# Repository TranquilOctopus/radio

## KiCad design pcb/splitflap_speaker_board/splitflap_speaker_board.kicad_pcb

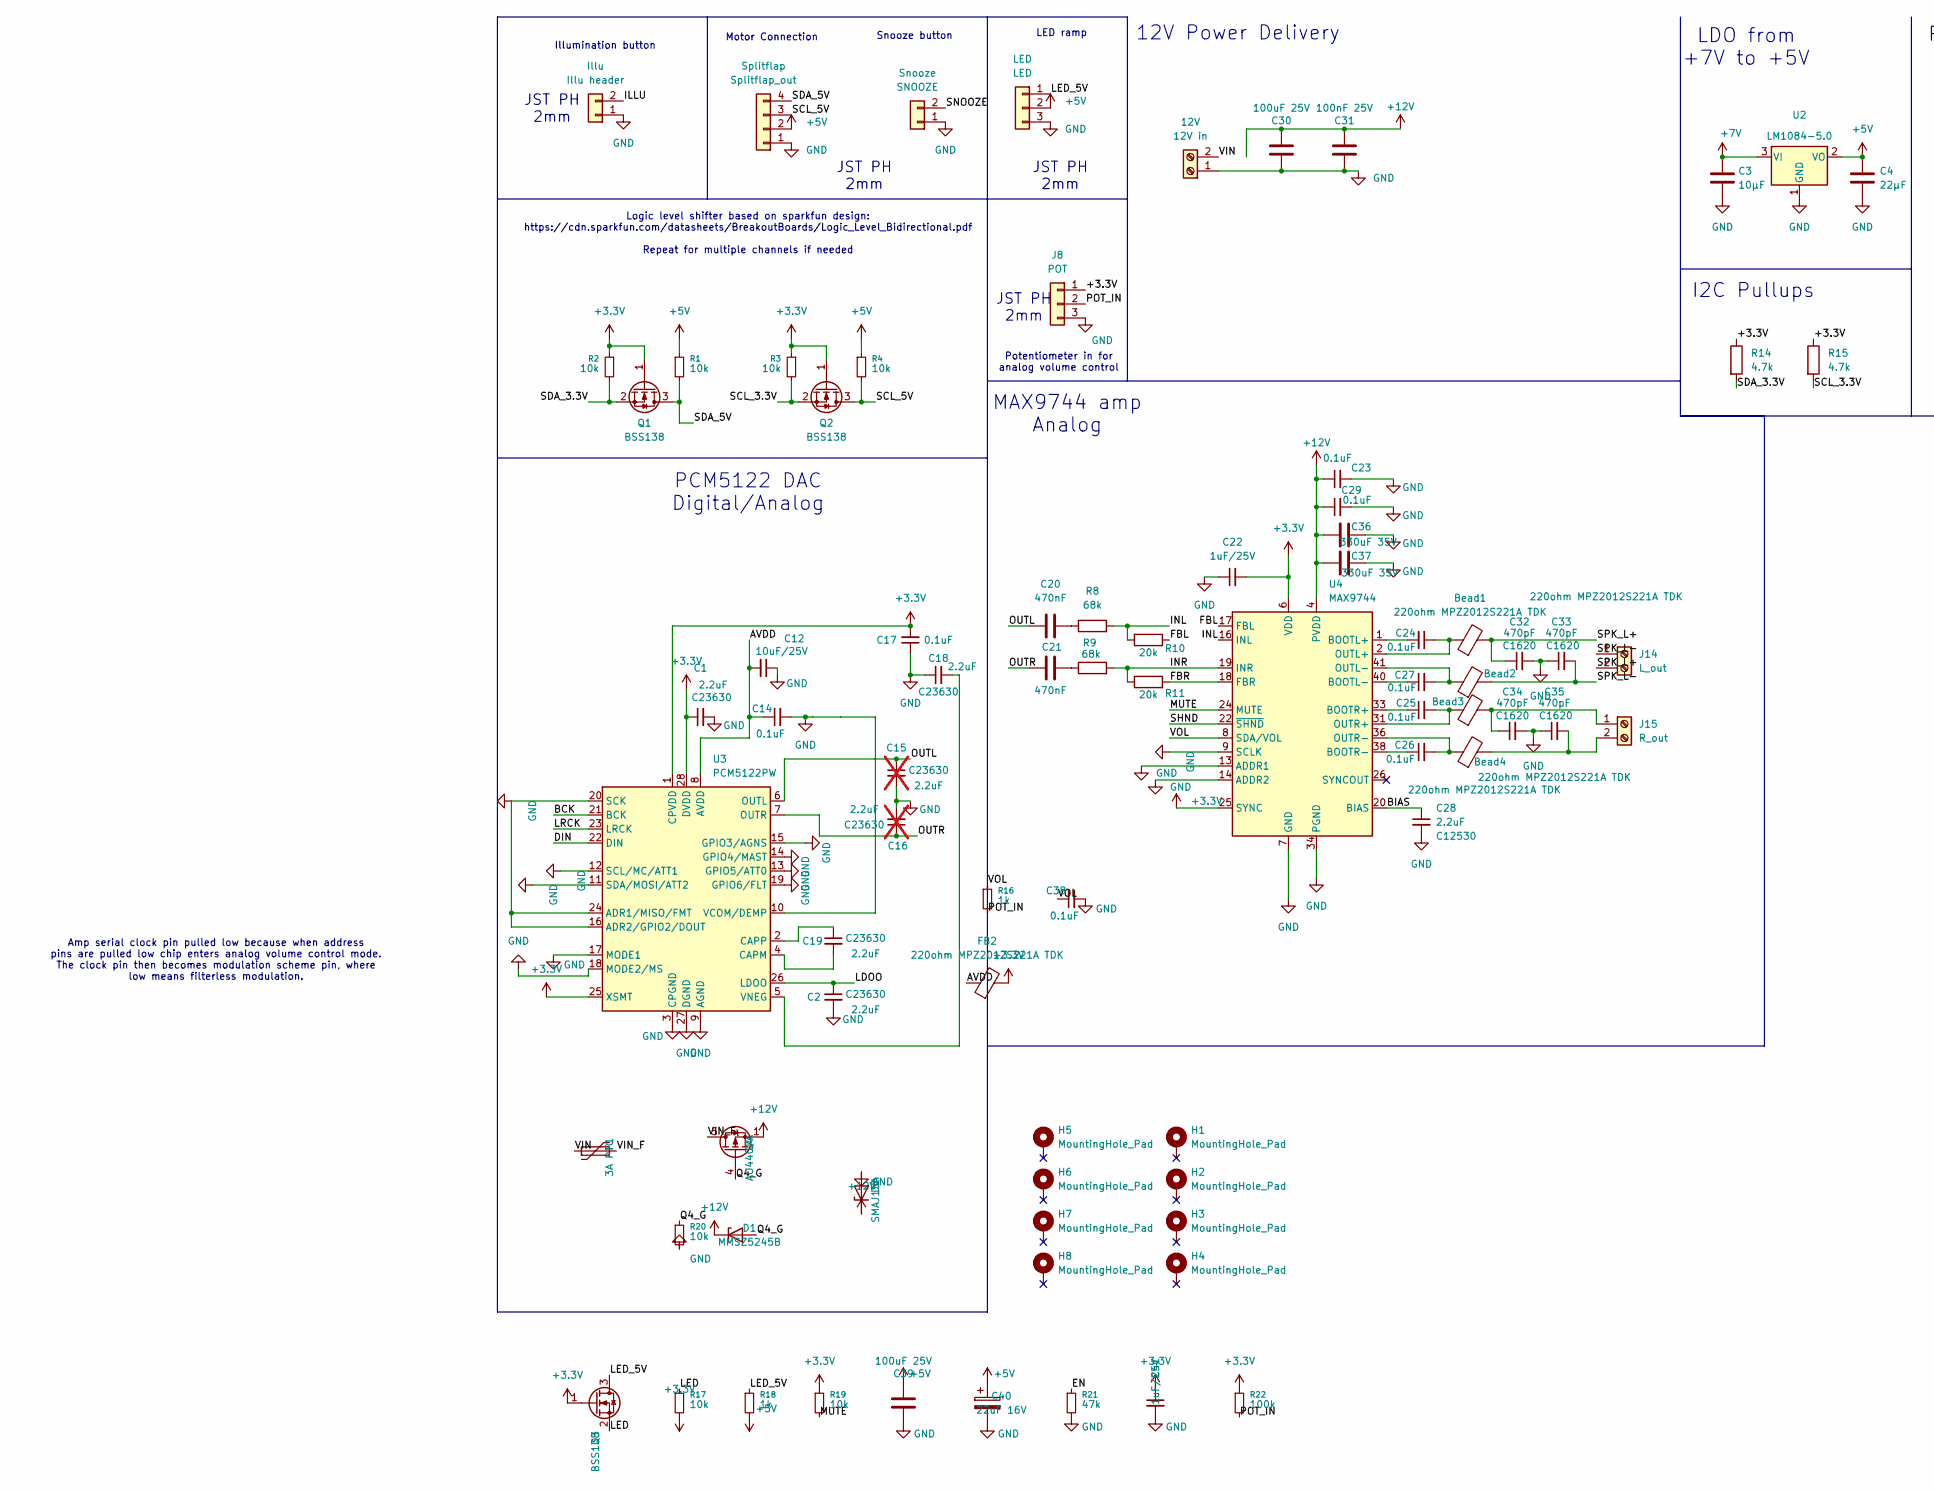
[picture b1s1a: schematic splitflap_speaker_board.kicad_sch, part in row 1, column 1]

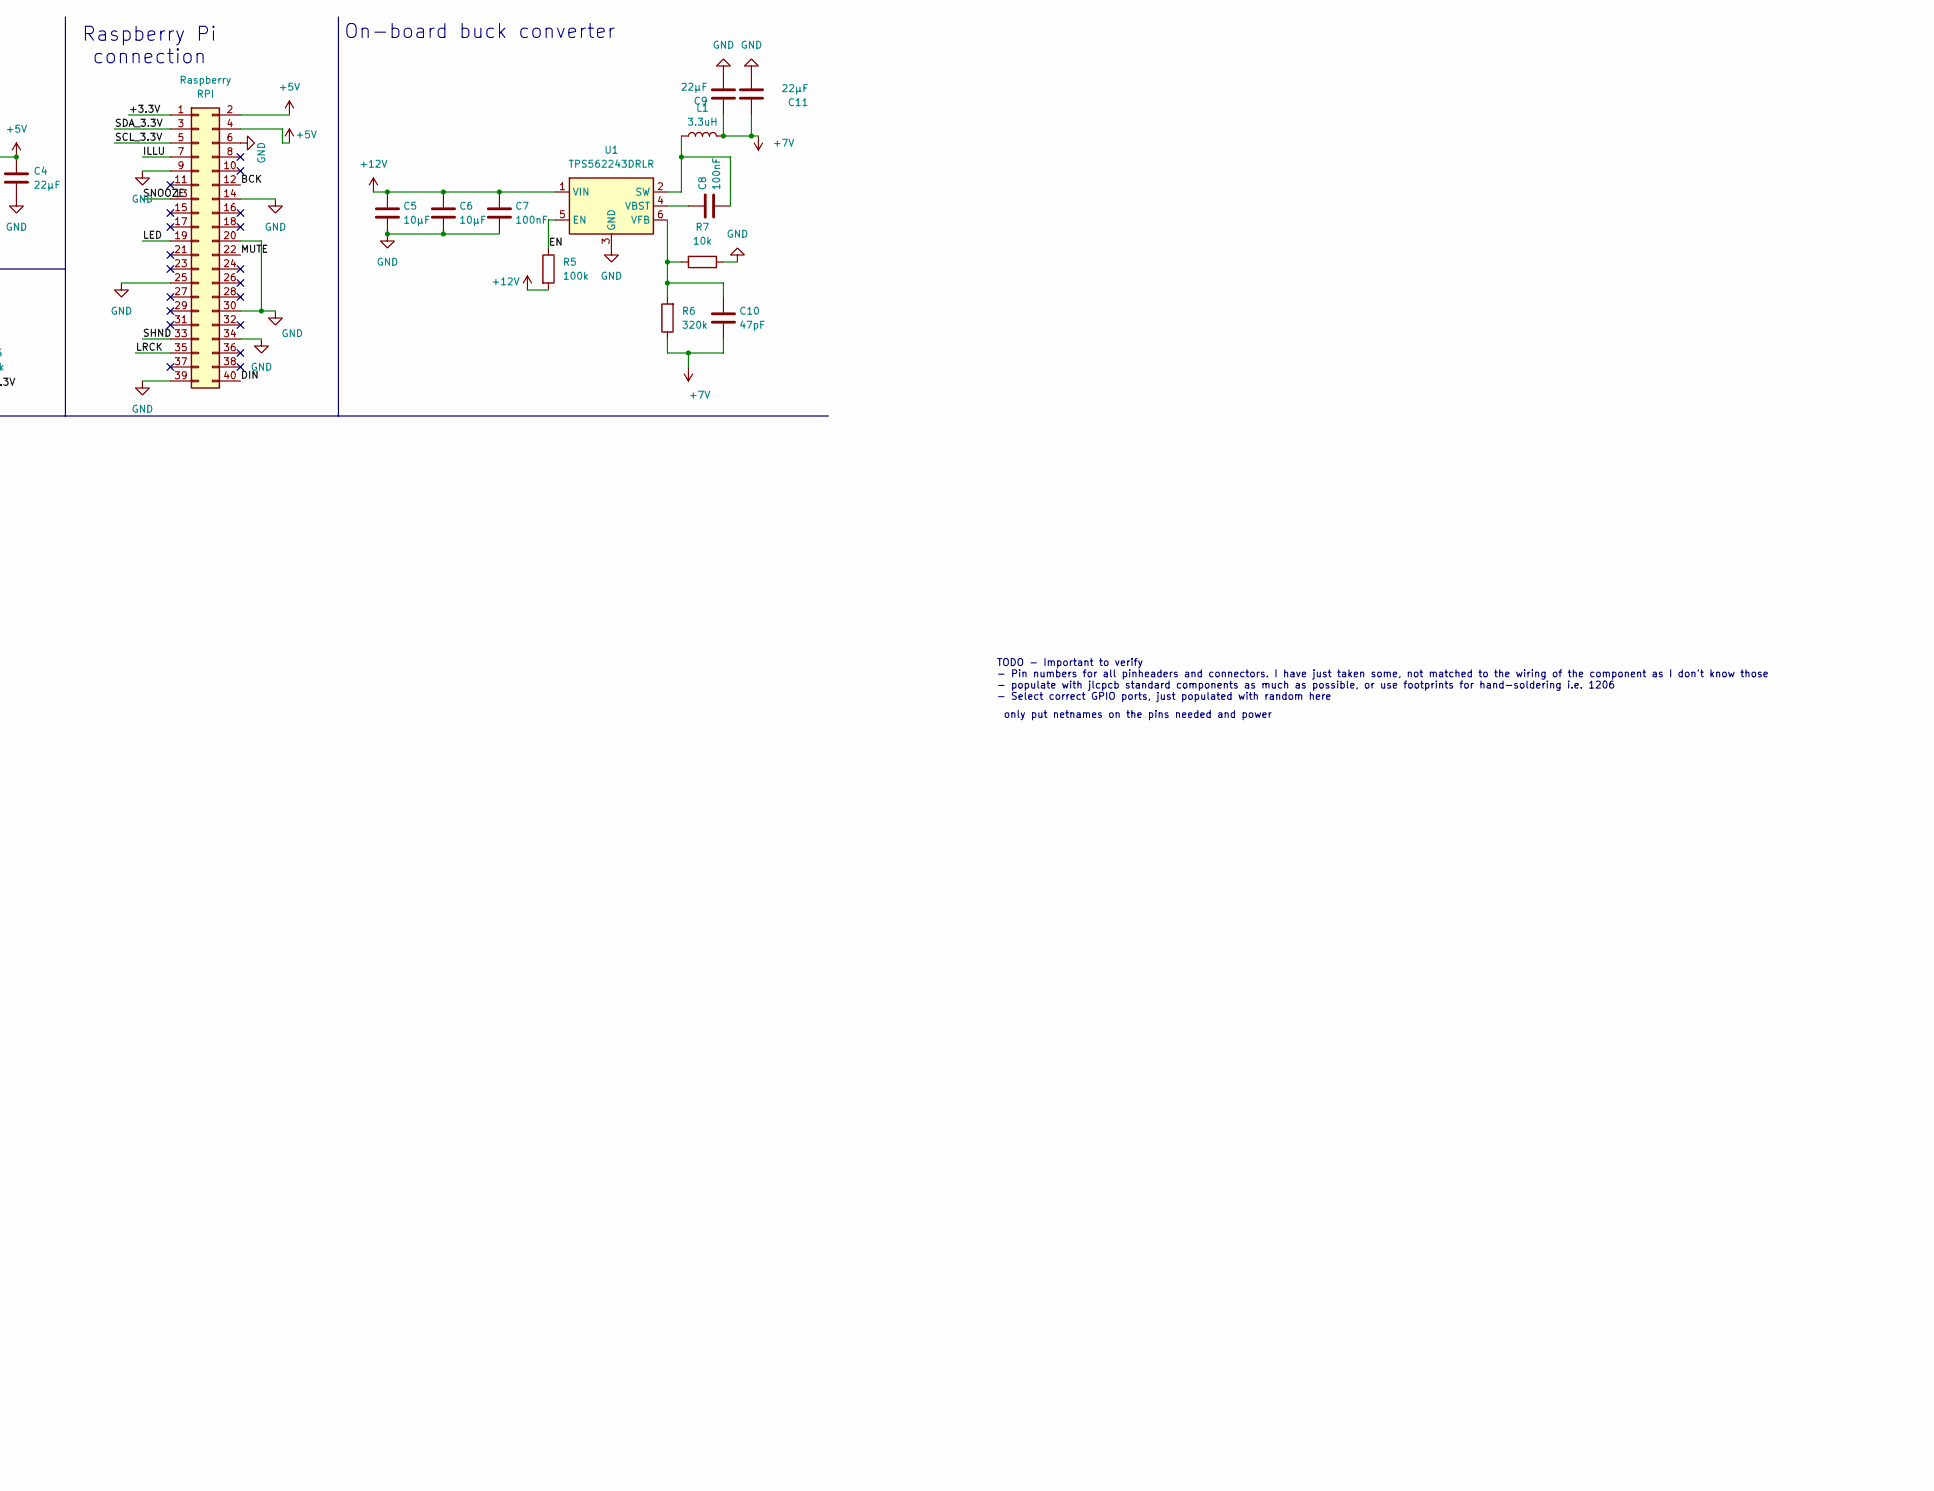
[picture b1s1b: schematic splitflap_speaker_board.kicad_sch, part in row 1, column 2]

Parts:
12V: 12V in; TerminalBlock_4Ucon_1x02_P3.50mm_Horizontal; LCSC C695629
Bead1, Bead2, Bead3, Bead4: 220ohm MPZ2012S221A TDK; L_0805_2012Metric; LCSC C76818
C1, C2, C18, C19: 2.2uF_0603_16V; C_0603_1608Metric; Part Number CL10A225KO8NNNC; JLCPCB ID C23630
C3: 10μF; C_0603_1608Metric; LCSC C96446
C4, C9, C11: 22μF; C_0805_2012Metric; LCSC C45783
C5, C6: 10μF; C_0805_2012Metric; LCSC C15850
C7, C8: 100nF; C_0603_1608Metric; LCSC C14663
C10: 47pF; C_0603_1608Metric; LCSC C1671
C12: 10uF_0805_25V; C_0805_2012Metric; Part Number GRM21BR61E106MA73L; JLCPCB ID C15850
C14, C17, C23, C29, C38: 0.1uF_0603_16V; C_0603_1608Metric; Part Number 0603YC104KAT2A; JLCPCB ID C14663
C15, C16: 2.2uF_0603_16V; C_0603_1608Metric; Part Number CL10A225KO8NNNC; JLCPCB ID C23630; not fitted
C20, C21: 470nF; C_0603_1608Metric; LCSC C1623
C22, C41: 1uF_0603_25V; C_0603_1608Metric; Part Number GRM188R61E105KA12D; JLCPCB ID C15849
C24, C25, C26, C27: 0.1uF_0805_50V; C_0805_2012Metric; Part Number CC0805KRX7R9BB104; JLCPCB ID C49678
C28: 2.2uF_0402_6.3V; C_0402_1005Metric; Part Number CL05A225MQ5NSNC; JLCPCB ID C12530
C30, C39: 100uF 25V; C_1210_3225Metric; LCSC C394395
C31: 100nF 25V; C_0402_1005Metric; LCSC C307331
C32, C33, C34, C35: 470pF_0603_50V; C_0603_1608Metric; Part Number 0603B471K500NT; JLCPCB ID C1620
C36, C37: 330uF 35V; C_Elec_10x10.2; LCSC C2895285
C40: 22uF 16V; CP_EIA-3528-21_Kemet-B; LCSC C8020
D1: MMSZ5245B; D_SOD-123; LCSC C2126
D2: SMAJ15A; D_SMA; LCSC C571368
F1: 3A PTC; Fuse_1812_4532Metric; LCSC C883162
FB2: 220ohm MPZ2012S221A TDK; L_0805_2012Metric; LCSC C76818
H1, H2, H3, H4: MountingHole_Pad; MountingHole_3.2mm_M3_DIN965_Pad
H5, H6, H7, H8: MountingHole_Pad; MountingHole_2.7mm_M2.5_Pad
Illu: Illu header; JST_PH_B2B-PH-K_1x02_P2.00mm_Vertical; LCSC C131337
J8: POT; JST_PH_B3B-PH-K_1x03_P2.00mm_Vertical; LCSC C131339
J14: L_out; TerminalBlock_4Ucon_1x02_P3.50mm_Horizontal; LCSC C695629
J15: R_out; TerminalBlock_4Ucon_1x02_P3.50mm_Horizontal; LCSC C695629
L1: 3.3uH; L_Bourns_SRN6045TA; LCSC C3221229
LED: LED; JST_PH_B3B-PH-K_1x03_P2.00mm_Vertical; LCSC C131339
Q1, Q2, Q3: BSS138; TSOT-23; LCSC C7420339
Q4: AO4407A; SOIC-8_3.9x4.9mm_P1.27mm; LCSC C16072
R1, R2, R3, R4, R17, R19, R20: 10k; R_0603_1608Metric; LCSC C25804
R5, R6: 100k_0603; R_0603; Part Number RC0603FR-07100KL; JLCPCB ID C25803
R7: 10k; R_0603; Part Number RC0603FR-0710KL; JLCPCB ID C25804
R8, R9: 68k_0603; R_0603_1608Metric; Part Number 0603WAF6802T5E; JLCPCB ID C23231
R10, R11: 20k_0603; R_0603_1608Metric; Part Number RC0603FR-0720KL; JLCPCB ID C4184
R14, R15: 4.7k_0603; R_0603_1608Metric; Part Number RC0603FR-074K7L; JLCPCB ID C23162
R16, R18: 1k; R_0603_1608Metric; LCSC C21190
R21: 47k; R_0603_1608Metric; LCSC C25819
R22: 100k; R_0603_1608Metric; LCSC C25803
Raspberry: RPI; PinSocket_2x20_P2.54mm_Vertical_PiFaceUp; LCSC C50980
Snooze: SNOOZE; JST_PH_B2B-PH-K_1x02_P2.00mm_Vertical; LCSC C131337
Splitflap: Splitflap_out; JST_PH_B4B-PH-K_1x04_P2.00mm_Vertical; LCSC C131334
U1: TPS562243DRLR; SOT-563; LCSC C42295941
U2: LM1084-5.0; TO-220-3_Vertical; LCSC C7432322
U3: PCM5122PW; TSSOP-28_4.4x9.7mm_P0.65mm; LCSC C962071
U4: MAX9744; TQFN-44-1EP_7x7mm_P0.5mm_EP4.7x4.7mm_ThermalVias; LCSC C4991234

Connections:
+3.3V: C1.1, C17.2, C22.2, C41.1, FB2.2, J8.1, Q1.1 (G), Q2.1 (G), Q3.1 (G), R2.1, R3.1, R14.1, R15.1, R17.2, R19.1, R22.1, Raspberry.1, U3.1 (CPVDD), U3.25 (XSMT), U3.28 (DVDD), U4.6 (VDD), U4.10 (VDD), U4.21 (VDD), U4.25 (SYNC), U4.28 (VDD)
+5V: C4.1, C39.1, C40.1, LED.2, R1.1, R4.1, R18.2, Raspberry.2, Raspberry.4, Splitflap.2, U2.2 (VO)
+7V: C3.1, C9.1, C10.2, C11.1, L1.2, R6.1, U2.3 (VI)
+12V: C5.1, C6.1, C7.1, C23.1, C29.1, C30.2, C31.2, C36.1, C37.1, D1.1 (K), D2.1 (K), Q4.1 (S), Q4.2 (S), Q4.3 (S), R5.2, U1.1 (VIN), U4.4 (PVDD), U4.5 (PVDD), U4.29 (PVDD), U4.30 (PVDD)
/AVDD: C12.2, C14.1, FB2.1, U3.8 (AVDD)
/BCK: Raspberry.12, U3.21 (BCK)
/BIAS: C28.1, U4.20 (BIAS)
/DIN: Raspberry.40, U3.22 (DIN)
/EN: R5.1, R21.1, U1.5 (EN)
/FBL: R10.1, U4.17 (FBL)
/FBR: R11.2, U4.18 (FBR)
/ILLU: Illu.2, Raspberry.7
/INL: R8.2, R10.2, U4.16 (INL)
/INR: R9.2, R11.1, U4.19 (INR)
/LDOO: C2.1, U3.26 (LDOO)
/LED: Q3.2 (S), R17.1, Raspberry.19
/LED_5V: LED.1, Q3.3 (D), R18.1
/LRCK: Raspberry.35, U3.23 (LRCK)
/MUTE: R19.2, Raspberry.22, U4.24 (MUTE)
/OUTL: C15.1, C20.1, U3.6 (OUTL)
/OUTR: C16.1, C21.1, U3.7 (OUTR)
/POT_IN: J8.2, R16.2, R22.2
/Q4_G: D1.2 (A), Q4.4 (G), R20.1
/SCL_3.3V: Q2.2 (S), R3.2, R15.2, Raspberry.5
/SCL_5V: Q2.3 (D), R4.2, Splitflap.3
/SDA_3.3V: Q1.2 (S), R2.2, R14.2, Raspberry.3
/SDA_5V: Q1.3 (D), R1.2, Splitflap.4
/SHND: Raspberry.33, U4.22 (~SHND)
/SNOOZE: Raspberry.13, Snooze.2
/VIN: 12V.2, F1.1
/VIN_F: F1.2, Q4.5 (D), Q4.6 (D), Q4.7 (D), Q4.8 (D)
/VOL: C38.1, R16.1, U4.8 (SDA/VOL)
GND: 12V.1, C1.2, C2.2, C3.2, C4.2, C5.2, C6.2, C7.2, C9.2, C11.2, C12.1, C14.2, C15.2, C16.2, C17.1, C18.1, C22.1, C23.2, C28.2, C29.2, C30.1, C31.1, C32.2, C33.1, C34.2, C35.1, C36.2, C37.2, C38.2, C39.2, C40.2, C41.2, D2.2 (A), Illu.1, J8.3, LED.3, R7.1, R20.2, R21.2, Raspberry.6, Raspberry.9, Raspberry.14, Raspberry.20, Raspberry.25, Raspberry.30, Raspberry.34, Raspberry.39, Snooze.1, Splitflap.1, U1.3 (GND), U2.1 (GND), U3.3 (CPGND), U3.9 (AGND), U3.10 (VCOM/DEMP), U3.11 (SDA/MOSI/ATT2), U3.12 (SCL/MC/ATT1), U3.13 (GPIO5/ATT0), U3.14 (GPIO4/MAST), U3.15 (GPIO3/AGNS), U3.16 (ADR2/GPIO2/DOUT), U3.17 (MODE1), U3.18 (MODE2/MS), U3.19 (GPIO6/FLT), U3.20 (SCK), U3.24 (ADR1/MISO/FMT), U3.27 (DGND), U4.7 (GND), U4.9 (SCLK), U4.11 (GND), U4.12 (GND), U4.13 (ADDR1), U4.14 (ADDR2), U4.15 (GND), U4.27 (GND), U4.34 (PGND), U4.35 (PGND), U4.39 (PGND), U4.43 (PGND), U4.44 (PGND), U4.45 (EP)
unnamed: Bead1.1, C24.1, U4.2 (OUTL+), U4.3 (OUTL+)
unnamed: Bead2.1, C27.2, U4.41 (OUTL-), U4.42 (OUTL-)
unnamed: Bead3.1, C25.2, U4.31 (OUTR+), U4.32 (OUTR+)
unnamed: Bead4.1, C26.2, U4.36 (OUTR-), U4.37 (OUTR-)
unnamed: C20.2, R8.1
unnamed: C21.2, R9.1
unnamed: Bead1.2, C32.1, J14.2
unnamed: Bead2.2, C33.2, J14.1
unnamed: Bead3.2, C34.1, J15.1
unnamed: Bead4.2, C35.2, J15.2
unnamed: C8.2, L1.1, U1.2 (SW)
unnamed: C8.1, U1.4 (VBST)
unnamed: C10.1, R6.2, R7.2, U1.6 (VFB)
unnamed: C19.2, U3.4 (CAPM)
unnamed: C19.1, U3.2 (CAPP)
unnamed: C18.2, U3.5 (VNEG)
unnamed: C24.2, U4.1 (BOOTL+)
unnamed: C27.1, U4.40 (BOOTL-)
unnamed: C25.1, U4.33 (BOOTR+)
unnamed: C26.1, U4.38 (BOOTR-)

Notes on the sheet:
Potentiometer in for analog volume control
only put netnames on the pins needed and power
Illumination button
JST PH 2mm
TODO - Important to verify - Pin numbers for all pinheaders and connectors. I have just taken some, not matched to the wiring of the component as I don't know those - populate with jlcpcb standard components as much as possible, or use footprints for hand-soldering i.e. 1206 - Select correct GPIO p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
LDO from +7V to +5V
MAX9744 amp Analog
Amp serial clock pin pulled low because when address pins are pulled low chip enters analog volume control mode. The clock pin then becomes modulation scheme pin, where low means filterless modulation.
12V Power Delivery
PCM5122 DAC Digital/Analog
Logic level shifter based on sparkfun design: https://cdn.sparkfun.com/datasheets/BreakoutBoards/Logic_Level_Bidirectional.pdf Repeat for multiple channels if needed
LED ramp
I2C Pullups
Snooze button
Motor Connection
On-board buck converter
Raspberry Pi connection

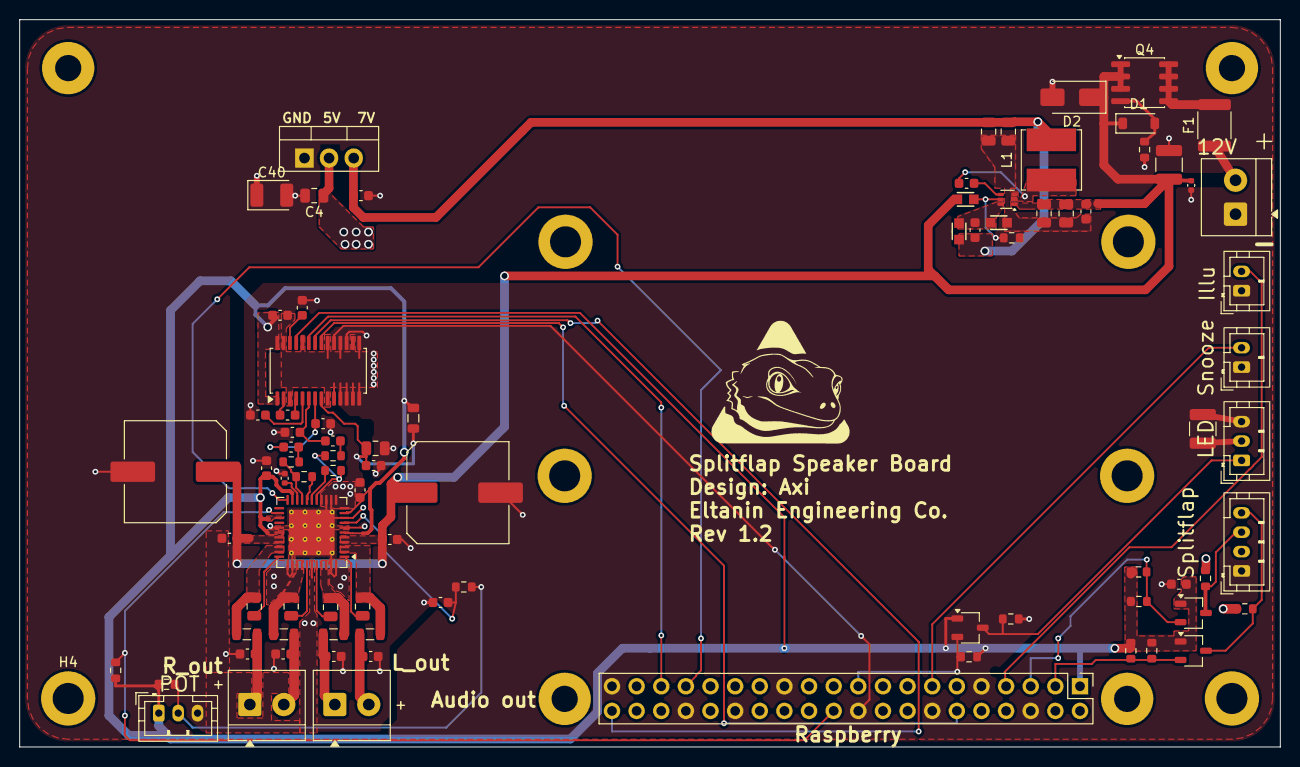
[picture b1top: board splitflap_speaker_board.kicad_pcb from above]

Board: 4 copper layers, 130.0 x 75.0 mm, 96 parts (0 on the bottom side), 53 nets.

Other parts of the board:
H1#2, H1#3: MountingHole_Pad; MountingHole_3.2mm_M3_DIN965_Pad

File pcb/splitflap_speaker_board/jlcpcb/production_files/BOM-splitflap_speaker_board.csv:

Comment,Designator,Footprint,LCSC,Quantity
0.1uF_0603_16V,"C14,C17,C23,C29",C_0603_1608Metric,C14663,4
0.1uF_0603_16V,"C24,C25,C26,C27",C_0805_2012Metric,C49678,4
0.1μF,"C7,C8",C_0603_1608Metric,C14858,2
100k_0603,"R5,R6,R7",R_0603,C25803,3
100nF 25V,C31,C_0402_1005Metric,C307331,1
100uF 25V,C30,C_1210_3225Metric,C394395,1
10k,"R1,R2,R3,R4",R_0603_1608Metric,C25804,4
10uF_0805_25V,"C12,C13",C_0805_2012Metric,C15850,2
10μF,"C5,C6",C_0805_2012Metric,C15850,2
10μF,C3,C_0603_1608Metric,C96446,1
12V in,12V_in,TerminalBlock_4Ucon_1x02_P3.50mm_Horizontal,C695629,1
1uF_0603_25V,C22,C_0603_1608Metric,C15849,1
2.2uF_0603_35V,C28,C_0201_0603Metric,C23630,1
2.2uF_0603_35V,"C1,C15,C16,C18,C19,C2",C_0603_1608Metric,C57895,6
20k_0603,"R10,R11,R8,R9",R_0603_1608Metric,C4184,4
220ohm MPZ2012S221A TDK,"Bead1,Bead2,Bead3,Bead4",L_0805_2012Metric,C21286,4
22μF,"C11,C4,C9",C_0805_2012Metric,C45783,3
3.3uH,L1,L_0603_1608Metric,C1329900,1
330uF,"C36,C37",C_Elec_10x10.2,C165451,2
4.7k_0603,"R14,R15",R_0603_1608Metric,C23162,2
470nF,"C20,C21",C_0603_1608Metric,C1623,2
470pF_0603_25V,"C32,C33,C34,C35",C_0805_2012Metric,C1620,4
47pF,C10,C_0603_1608Metric,C1671,1
BSS138,"Q1,Q2",TSOT-23,C7420339,2
Illu header,Light,JST_PH_B2B-PH-K_1x02_P2.00mm_Vertical,C131337,1
LED,LED,JST_PH_B3B-PH-K_1x03_P2.00mm_Vertical,C131339,1
LM1084-5.0,U2,TO-220-3_Vertical,C7432322,1
L_out,J14,TerminalBlock_4Ucon_1x02_P3.50mm_Horizontal,C695629,1
MAX9744,U4,TQFN-44-1EP_7x7mm_P0.5mm_EP4.7x4.7mm_ThermalVias,C4991234,1
PCM5122PW,U3,TSSOP-28_4.4x9.7mm_P0.65mm,C962071,1
POT,J8,JST_PH_B3B-PH-K_1x03_P2.00mm_Vertical,C131339,1
RPI,Raspberry_Pi,PinHeader_2x20_P2.54mm_Vertical,C50980,1
R_out,J15,TerminalBlock_4Ucon_1x02_P3.50mm_Horizontal,C695629,1
SNOOZE,Snooze,JST_PH_B2B-PH-K_1x02_P2.00mm_Vertical,C131337,1
Splitflap_out,Splitflaps,JST_PH_B4B-PH-K_1x04_P2.00mm_Vertical,C131334,1
TPS562243DRLR,U1,SOT-563,C42295941,1

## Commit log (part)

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2026-04-27 Document microSD card size requirements
    Add a setup section covering Pi OS Lite choice, disk usage budget, and
    recommended card sizes (16 GB sweet spot) so the build BOM has a concrete
    target instead of guessing.
2026-04-28 Use 'admin' as the deployment user
    Replace the hard-coded /home/alex paths with /home/admin in the systemd
    unit and setup notes so a fresh Pi flashed with the 'admin' user works
    without manual edits.
2026-04-28 Fall back to mock LED strip on rpi_ws281x init failure
    ws2811_init can raise RuntimeError at runtime even when the library
    imports cleanly (e.g. unrecognised Pi revision, no /dev/mem access).
    Currently this kills the whole service on boot. Catch the error,
    swap in MockPixelStrip, and keep the rest of the stack alive — same
    spirit as the existing ImportError fallback.
2026-04-28 Probe I2C bus before initialising splitflap and potentiometer
    Both subsystems crashed the service with OSError EIO when their PCF8575s
    or ADS1115 weren't physically wired up — fine on a finished build,
    fatal during early bring-up. Probe each subsystem's addresses; if
    nothing ACKs, swap in MockSMBus so the rest of the stack (web UI,
    radio, alarm) still comes up.
2026-04-28 Fix scheduler crash by removing bogus timezone='local' kwarg
    APScheduler tried to resolve 'local' as an IANA zone name, fell
    through to importing the tzdata package, and crashed with
    ZoneInfoNotFoundError on a Pi that has neither. Drop the kwarg so
    APScheduler uses tzlocal.get_localzone() (system /etc/localtime),
    which gives us a real zone name and DST-safe rescheduling. Update
    CLAUDE.md so the next reader doesn't repeat the mistake.
2026-04-28 Switch LED driver to adafruit-circuitpython-neopixel-spi
    rpi_ws281x rejects Pi 3A+ rev 1.1 (revision 9020e1) because its
    hard-coded board table only knows the rev-1.0 code (9020e0). Rather
    than patch that table for every new Pi revision, switch to
    neopixel_spi which shifts WS281x timing out of the SPI peripheral
    and works on any Pi without hardware-revision detection.
    Wiring is unchanged — strip data still on GPIO 10 (SPI0 MOSI).
2026-04-28 Switch buttons from RPi.GPIO to gpiozero
    RPi.GPIO is unmaintained and its add_event_detect fails with
    'Failed to add edge detection' on Bookworm/Trixie kernels. Move
    to gpiozero (RPi Foundation's library, lgpio backend) which works
    across all current Pi OS releases. Wrap construction in try/except
    so init failures degrade to disabled buttons rather than crashing
    the service — matching the project's hardware-fallback convention.
2026-04-28 Add rpi-lgpio so adafruit-blinka can import on Trixie
    neopixel_spi pulls in adafruit-blinka, which probes the platform by
    importing RPi.GPIO. We dropped RPi.GPIO when switching buttons to
    gpiozero, breaking Blinka's import. rpi-lgpio is a drop-in shim that
    provides the RPi.GPIO import name on top of lgpio — Blinka is happy
    and we avoid the broken add_event_detect path.
2026-04-28 Use new Starlette TemplateResponse signature
    The first positional arg is now the Request, not the template name.
    The old form silently misroutes — Starlette treats the dict as the
    template name and Jinja chokes with 'unhashable type: dict' on the
    cache lookup.
2026-04-28 Make LED strip type configurable (WS2812 vs SK6812)
    Add config.yaml:led.strip_type with values "WS2812" (RGB, 3 channels)
    or "SK6812" (RGBW, 4 channels). The driver picks the right pixel
    order and tuple length at runtime so the same code drives either
    strip without recompilation. Default value in config is WS2812 since
    that's what's wired up first; the field default in build_led falls
    back to SK6812 for the planned final hardware.
2026-04-28 Set led.num_leds to 10 for current bench strip
    Match the 10-LED test strip wired up now; will bump to the final
    count when the cabinet's strip is fitted.
2026-04-29 LED button: fade-on hold-then-fade-off behaviour
    Replace the latching toggle with a courtesy-light pattern:
    - Press → smooth ramp up to configured brightness
    - Hold → strip stays at full brightness while button is held
    - Release → 5 s hold, then smooth ramp off
    - Re-press → cancels the off-timer and ramps back up
    LEDStrip gains fade_on/fade_off methods (cancellable, single fade
2026-05-01 Add MAX9744 amp control over I2C
    The amp's gain is now driven by software instead of whatever default
    the chip powered up at. Volume from the slide pot, the web slider,
    and (later) HomeKit all routes through Amp.set_volume() rather than
    MPD, so AirPlay benefits from the same control as MPD-sourced radio.
    A hardware ceiling (config.yaml: hardware.amp.max_volume, 0–63 in
    MAX9744 steps) caps how hot the amp can ever run, protecting the
2026-05-01 Fix ADS1115 I2C address: ADDR pin wired high gives 0x49 not 0x48
    https://claude.ai/code/session_015zaSE7d9HovSmnSjRWKPUA
2026-05-01 Add DAC HAT setup, bus 3 wiring guide, and fix ADS1115 address in README
    Documents dtoverlay=rpi-dacplus, shairport-sync alsa routing, PipeWire
    default sink config, and the bus 1 / bus 3 split layout with PCF8575
    address soldering table.
    https://claude.ai/code/session_015zaSE7d9HovSmnSjRWKPUA
2026-05-01 Move user I2C devices from bus 1 to bus 3
    Bus 1 is now exclusively for the DAC HAT (PCM5122, kernel-managed).
    PCF8575s, ADS1115, and MAX9744 all wire to the software I2C bus on
    GPIO 23/24.
    https://claude.ai/code/session_015zaSE7d9HovSmnSjRWKPUA
2026-05-01 Revert i2c_bus to 1 for soldered-PCF8575 setup
    With the PCF8575 address pads properly soldered (0x20-0x23, no
    collision), bus 1 has plenty of room for all devices alongside the
    DAC HAT and the built-in pull-ups remove the need for external
    resistors. Software I2C bus 3 stays available as a fallback.
    https://claude.ai/code/session_015zaSE7d9HovSmnSjRWKPUA
2026-05-09 podcast-brain: scaffold project + cross-platform Whisper backend
    New standalone subdirectory podcast-brain/ for the personal podcast
    knowledge system planned in /root/.claude/plans/. Scaffolds the typer
    CLI, pydantic config loader, and a hardware-portable Whisper backend
    with faster-whisper (CUDA/CPU) and mlx-whisper (Apple Silicon) impls
    behind a runtime-checkable protocol with lazy imports.
    https://claude.ai/code/session_01Qq7fZDyocaojEzNEpRhJJs
2026-05-09 podcast-brain: Kuzu graph layer + Obsidian vault writer
    Adds the two output sinks: a Kuzu-backed graph with idempotent upserts
    and merge-style edges (HOSTED_BY, GUEST, MENTIONS, CONTAINS, ABOUT,
    ASSERTED_BY, CONTRADICTS), and a markdown vault writer that emits
    Obsidian-compatible pages with YAML frontmatter and [[wikilinks]].
    regenerate_backlinks walks the graph to rewrite each entity's
    "Mentioned in" section. Wires the query CLI command. 19 tests pass.
2026-05-10 podcast-brain: ingest layer (PodcastIndex/iTunes/RSS) + SQLite queue + pacer
    Adds the input side of the pipeline:
    - pkm/queue.py: SQLite-backed feeds + jobs + claude_calls tables, WAL,
    upsert with ON CONFLICT, dedupe by (feed_id, episode_guid).
    - pkm/ingest/podcastindex.py: HMAC-SHA1 auth, search/lookup/episodes
    endpoints; injectable httpx for tests.
    - pkm/ingest/itunes.py: iTunes Search + Lookup; resolves
2026-05-10 podcast-brain: local LLM extractor + chunker + per-style schemas
    Adds the per-chunk extraction layer:
    - pkm/extract/chunker.py: sentence-aligned chunker (~3 min target,
    15s overlap) operating on Whisper Transcript dataclasses.
    - pkm/extract/schemas/{informational,banter,narrative}.py: pydantic
    models per show style; SCHEMA_BY_STYLE registry.
    - pkm/extract/prompts/styles/*.md: per-style system prompts loaded
2026-05-10 podcast-brain: entity canonicalization (slug dedupe + similarity)
    Adds pkm/extract/canonicalize.py: groups near-duplicate entity name
    strings (e.g. "JEPA"/"jepa", "Yann LeCun"/"Yann Lecun") into canonical
    entities by slug similarity using stdlib SequenceMatcher (no extra
    deps). Picks the most-frequent variant as the canonical name; ties
    broken by length. Configurable similarity threshold (default 0.85).
    Step 8 will call this once per entity type per episode before graph
2026-05-10 podcast-brain: Sonnet episode summarizer + budget tracker stub
    Adds the summarization layer:
    - pkm/summarize/episode.py: EpisodeSummarizer wrapping the Anthropic
    SDK with prompt caching (cache_control on system block), uses
    claude-sonnet-4-6 with effort=medium, max_tokens=4000.
    - pkm/summarize/base.py: EpisodeContext / EpisodeSummary pydantic
    models that bridge per-chunk extractions -> markdown body.
2026-05-10 podcast-brain: pipeline orchestrator + ingest CLI commands
    Wires every stage from Steps 2-7 into a single state machine:
    - pkm/pipeline.py: Pipeline class with advance_one/run_until_idle
    driving PENDING -> DOWNLOADED -> TRANSCRIBED -> CHUNKED ->
    EXTRACTED -> CANONICALIZED -> SUMMARIZED -> INDEXED -> DONE.
    Idempotent stages (re-runnable, artifact-cached on disk) and
    per-stage failure isolation that marks the job FAILED without
2026-05-10 podcast-brain: enforce monthly Claude spend cap + budget CLI
    Promotes the Step 7 BudgetTracker stub to actually enforce the cap:
    - can_spend() compares MTD spend (+ projected) against
    monthly_cap_usd; returns True when cap == 0 (unlimited).
    - mtd_remaining_usd() and usage_breakdown() for telemetry.
    - One-shot warning logged at warn_at_pct threshold per month.
    - Pipeline now passes BudgetConfig through to the tracker so
2026-05-10 podcast-brain: weekly cross-episode synthesizer + scheduler wire-up
    Adds the weekly digest pipeline:
    - pkm/summarize/synthesize.py: WeeklySynthesizer queries the graph
    for episodes in the week, recurring concepts (mentioned in 2+
    episodes), new people/orgs entering the corpus, and contradiction
    candidates (claims with opposite polarity about the same concept).
    Single Sonnet call composes a markdown digest; vault writer
2026-05-10 podcast-brain: OPML parser + URL ingest + watch-folder daemon
    Adds the auxiliary ingest sources:
    - pkm/ingest/opml.py: proper OPML walker handling both flat
    (Apple Podcasts) and nested-by-category (Overcast/Pocket Casts)
    layouts; refactors feed_import to use it.
    - pkm/ingest/url.py: yt-dlp wrapper for one-off audio URLs
    (YouTube, SoundCloud, episode pages); lazy-imports yt_dlp
2026-05-10 podcast-brain: FastAPI status dashboard + serve command
    Closes the loop with a small read-mostly dashboard at localhost:8765:
    - pkm/api.py: factory pattern create_app(config_path) with FastAPI
    Depends() providers for Queue / BudgetTracker / Config so tests can
    override. Routes: /api/health, /api/queue/{summary,jobs},
    /api/feeds, /api/feeds/{id}/style, /api/budget,
    /api/submit/{url,file}. URL submission uses BackgroundTasks so the
2026-05-10 podcast-brain: README - operating-it section
    Adds day-to-day operational docs: launchd/systemd unit examples,
    status + monitoring commands, FAILED/BUDGET_PAUSED recovery,
    restart safety guarantees, vault git workflow, audio pruning,
    DB vacuum, log rotation, model-switch implications, and a
    troubleshooting cheatsheet.
    https://claude.ai/code/session_01Qq7fZDyocaojEzNEpRhJJs
2026-05-10 podcast-brain: Discord bot + supporting REST endpoints
    Adds a slash-command Discord bot that lets you add podcasts and
    inspect queue / budget / digests from your phone:
    - pkm/bot/discord_bot.py: Discord client with /feed (add/search/list/style),
    /queue (status/jobs), /budget, /digest, /url slash commands.
    Hits the FastAPI dashboard over localhost; allowed_user_ids gate.
    - pkm/api.py: 3 new endpoints to support the bot —
